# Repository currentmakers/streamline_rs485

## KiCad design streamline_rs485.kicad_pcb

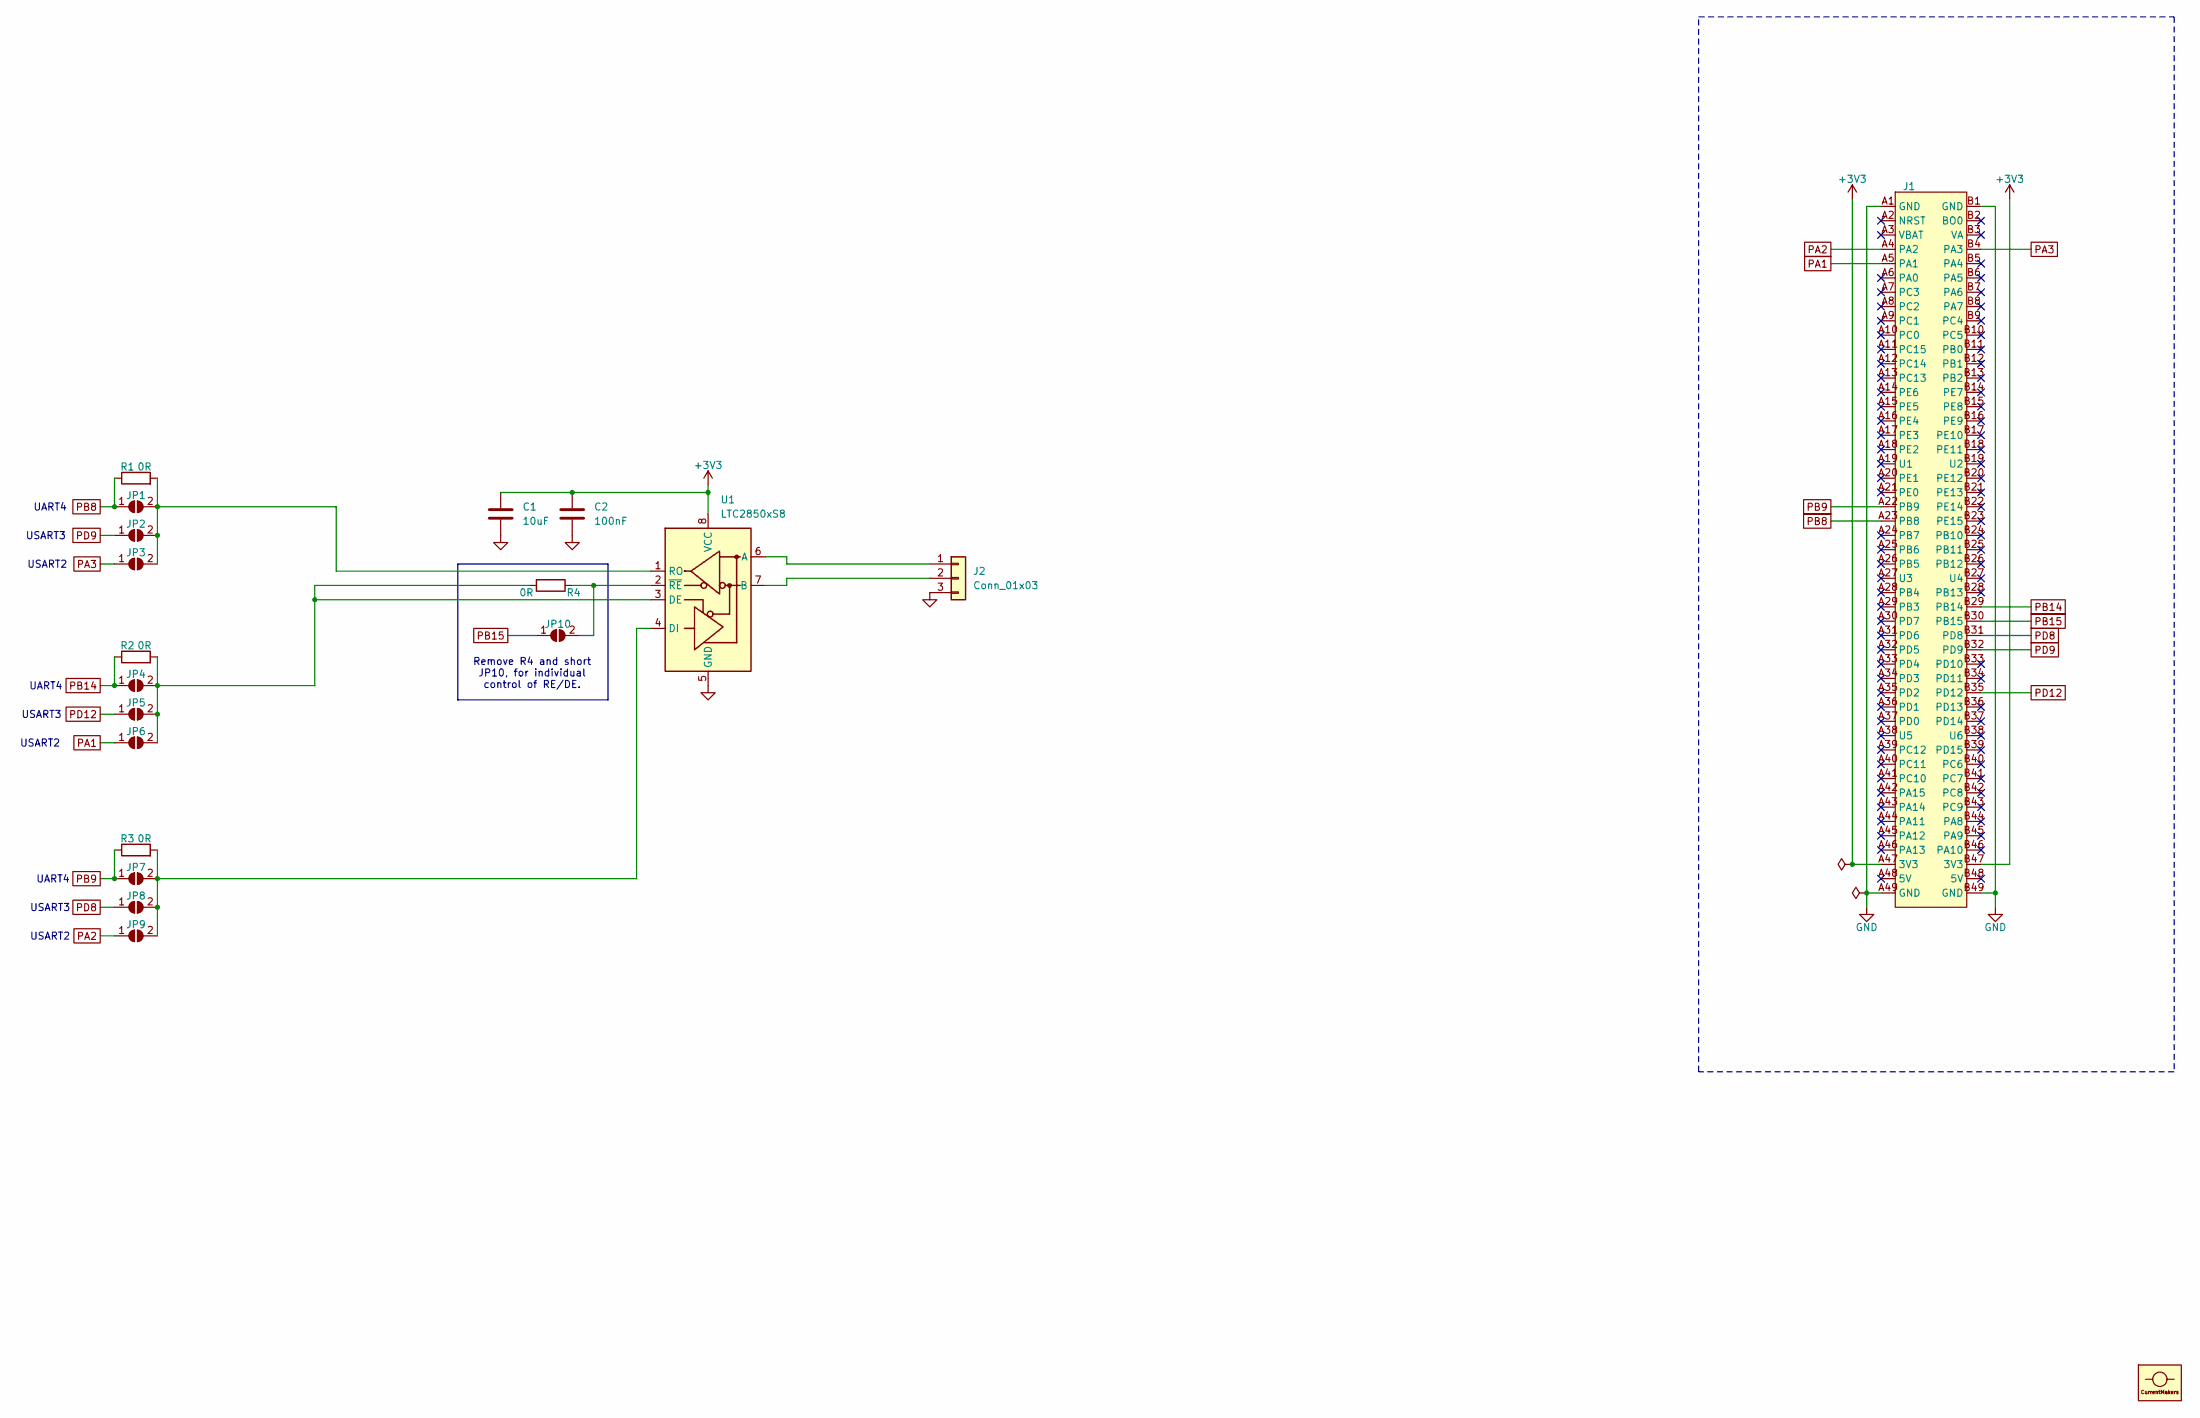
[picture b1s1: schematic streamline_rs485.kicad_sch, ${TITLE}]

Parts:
C1: 10uF; C_0805_2012Metric; LCSC C15850
C2: 100nF; C_0603_1608Metric; LCSC C14663
J1: SL_BOARD
J2: Conn_01x03; PhoenixContact_MSTBA_2,5_3-G-5,08_1x03_P5.08mm_Horizontal; MPN MSTBA 2,5/ 3-G-5,08; LCSC C5183941
JP1, JP2, JP3, JP4, JP5, JP6, JP7, JP8, JP9, JP10: SolderJumper_2_Open; SolderJumper-2_P1.3mm_Open_TrianglePad1.0x1.5mm
L1: cm_logo
R1, R2, R3, R4: 0R; R_0603_1608Metric; LCSC C21189
U1: LTC2850xS8; SOIC-8_3.9x4.9mm_P1.27mm

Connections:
+3V3: C1.1, C2.2, J1.A47 (3V3), J1.B47 (3V3), U1.8 (VCC)
GND: C1.2, C2.1, J1.A1 (GND), J1.A49 (GND), J1.B1 (GND), J1.B49 (GND), J2.3, U1.5 (GND)
unnamed: J2.1, U1.6 (A)
unnamed: J2.2, U1.7 (B)
unnamed: JP1.2 (B), JP2.2 (B), JP3.2 (B), R1.2, U1.1 (RO)
unnamed: JP4.2 (B), JP5.2 (B), JP6.2 (B), R2.2, R4.2, U1.3 (DE)
unnamed: JP7.2 (B), JP8.2 (B), JP9.2 (B), R3.2, U1.4 (DI)
unnamed: JP10.2 (B), R4.1, U1.2 (~RE)
PA1: J1.A5 (PA1), JP6.1 (A)
PA2: J1.A4 (PA2), JP9.1 (A)
PA3: J1.B4 (PA3), JP3.1 (A)
PB8: J1.A23 (PB8), JP1.1 (A), R1.1
PB9: J1.A22 (PB9), JP7.1 (A), R3.1
PB14: J1.B29 (PB14), JP4.1 (A), R2.1
PB15: J1.B30 (PB15), JP10.1 (A)
PD8: J1.B31 (PD8), JP8.1 (A)
PD9: J1.B32 (PD9), JP2.1 (A)
PD12: J1.B35 (PD12), JP5.1 (A)

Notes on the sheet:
USART2
USART3
UART4
Remove R4 and short JP10, for individual control of RE/DE.

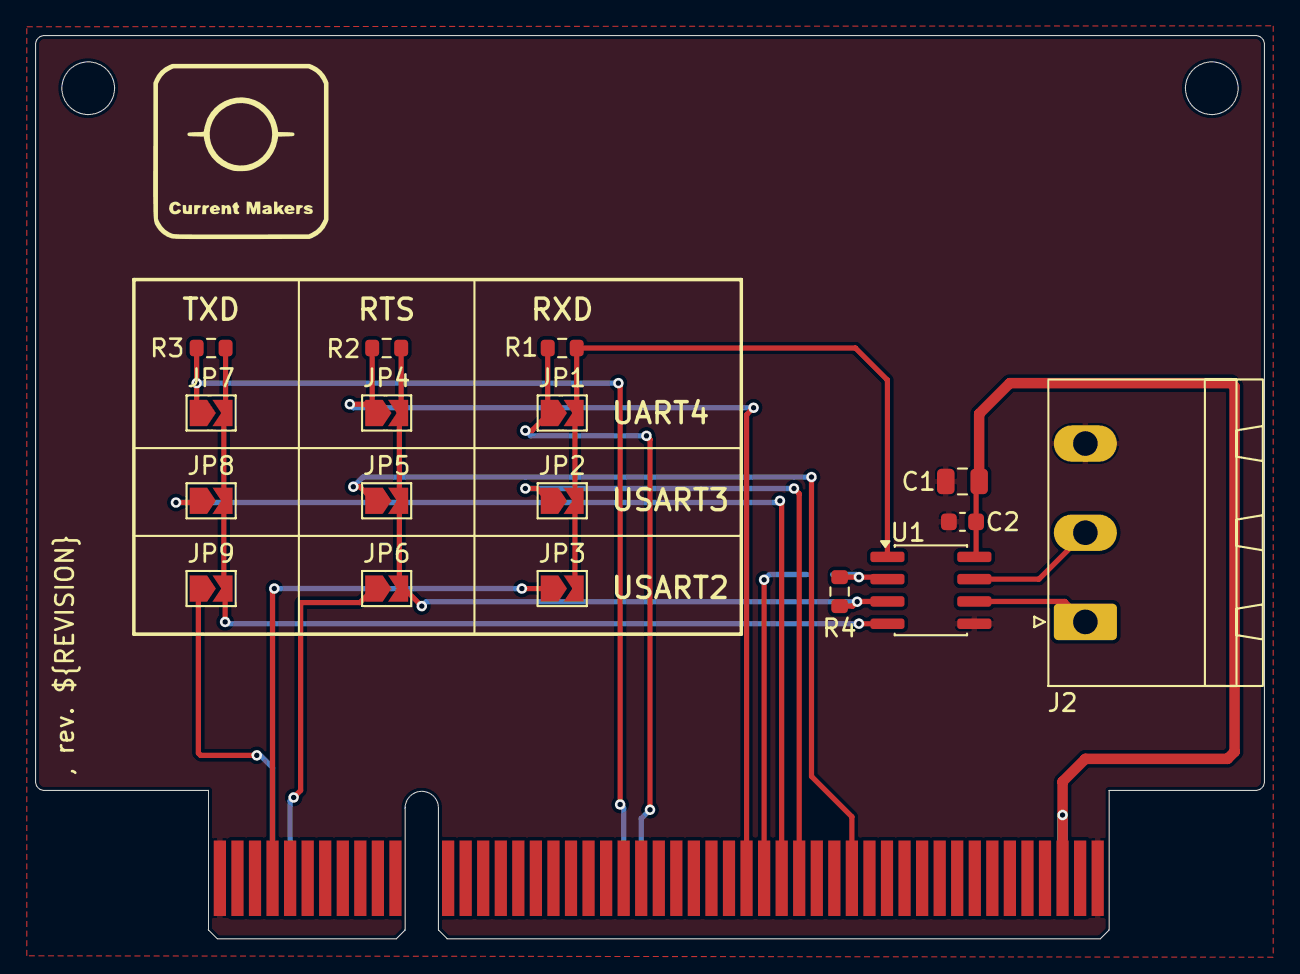
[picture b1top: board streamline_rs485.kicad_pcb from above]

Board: 2 copper layers, 70.0 x 51.5 mm, 20 parts (1 on the bottom side), 18 nets.

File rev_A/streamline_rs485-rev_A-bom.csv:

"Designator","Qty","Value","Footprint","LCSC"
"C1","1","10uF","Capacitor_SMD:C_0805_2012Metric","C15850"
"C2","1","100nF","Capacitor_SMD:C_0603_1608Metric","C14663"
"J2","1","Conn_01x03","Connector_Phoenix_MSTB:PhoenixContact_MSTBA_2,5_3-G-5,08_1x03_P5.08mm_Horizontal","C5183941"
"R1,R2,R3,R4","4","0R","Resistor_SMD:R_0603_1608Metric","C21189"
"U1","1","LTC2850xS8","Package_SO:SOIC-8_3.9x4.9mm_P1.27mm",""

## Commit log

2026-03-26 First draft
2026-03-29 Production files.
2026-05-27 Rev A
2026-06-21 Detected a serious flaw in the .gitignore file used.
2026-06-25 Added MF, MPN and LCSC info to RS-485 chip.
